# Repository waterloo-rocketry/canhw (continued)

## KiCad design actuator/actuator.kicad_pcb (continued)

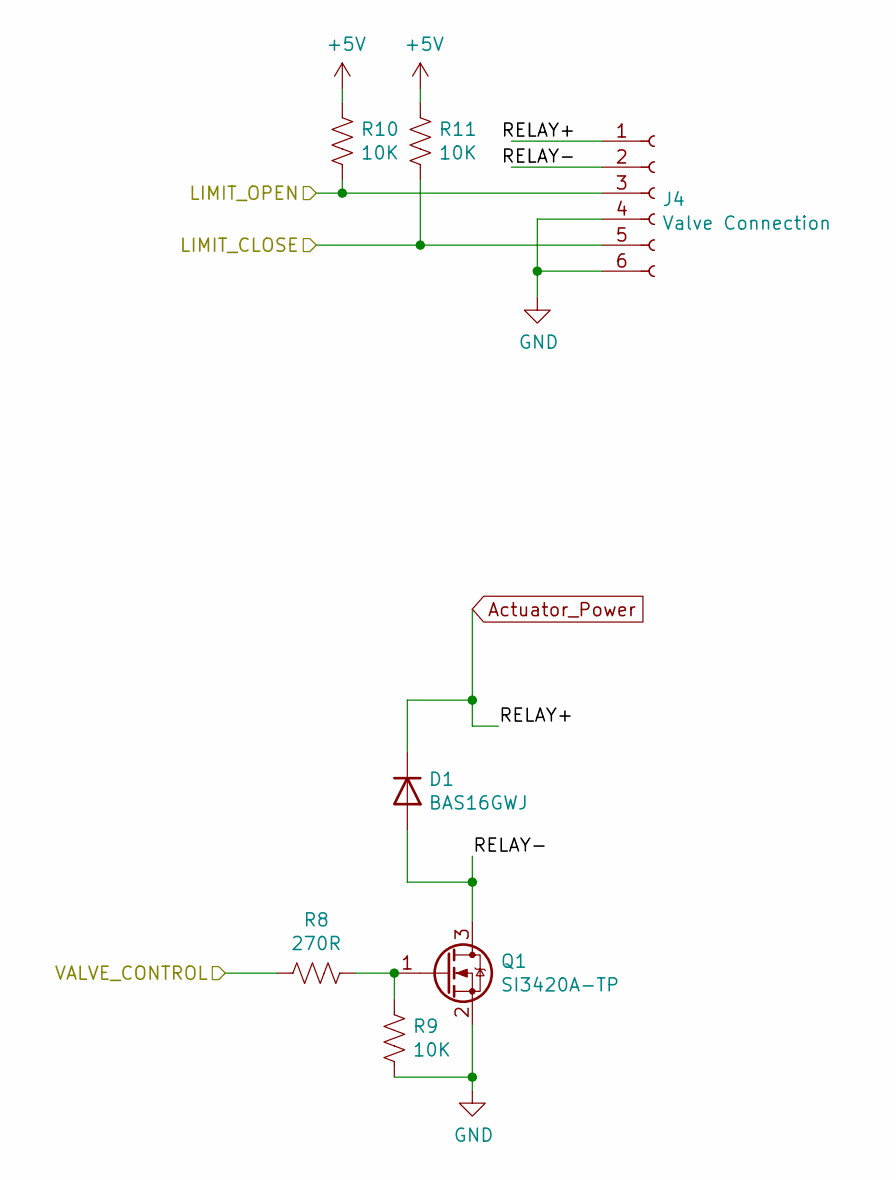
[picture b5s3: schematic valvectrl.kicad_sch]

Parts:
D1: BAS16GWJ; D_SOD-123
J4: Valve Connection; connector_Harwin_M80-5000642
Q1: SI3420A-TP; SOT-23_Handsoldering
R8: 270R; R_0805_2012Metric
R9, R10, R11: 10K; R_0805_2012Metric

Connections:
+5V: R10.1, R11.1; also elsewhere on the board
/MCU/LIMIT_CLOSE: J4.5, R11.2; also elsewhere on the board
/MCU/LIMIT_OPEN: J4.3, R10.2; also elsewhere on the board
/MCU/VALVE_CONTROL: R8.2; also elsewhere on the board
/Valve Control/RELAY-: D1.2 (A), J4.2, Q1.3 (D)
Actuator_Power: D1.1 (K), J4.1; also elsewhere on the board
GND: J4.4, J4.6, Q1.2 (S), R9.2; also elsewhere on the board
unnamed: Q1.1 (G), R8.1, R9.1

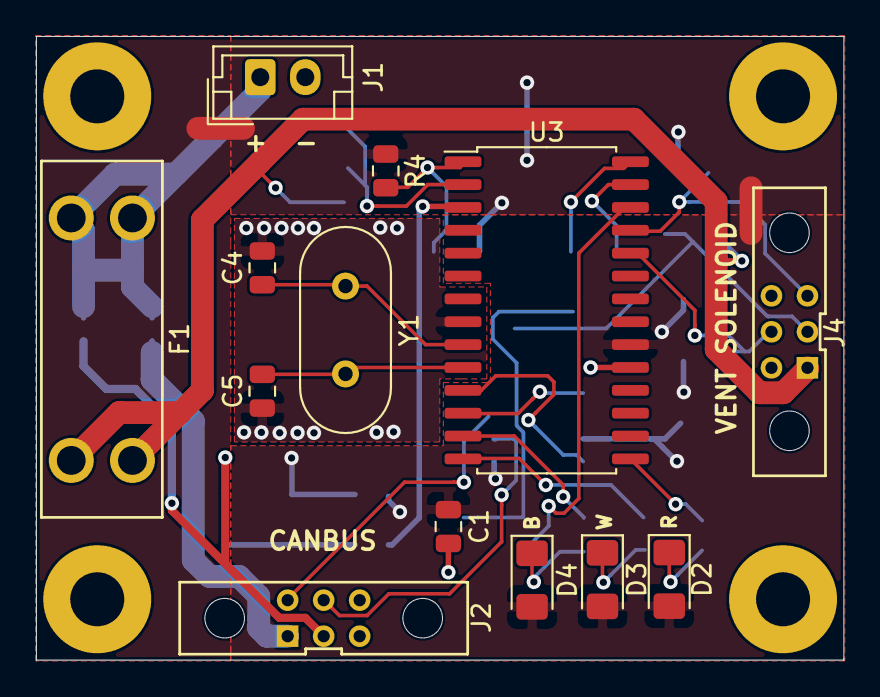
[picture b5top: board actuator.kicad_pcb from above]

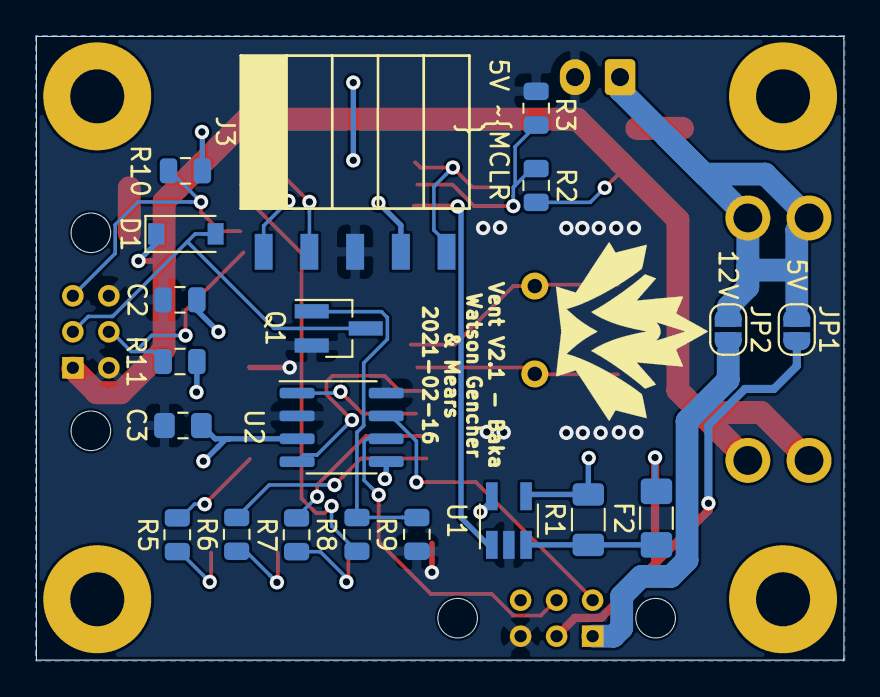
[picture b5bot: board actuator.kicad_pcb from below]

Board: 2 copper layers, 44.9 x 34.6 mm, 33 parts (20 on the bottom side), 29 nets.

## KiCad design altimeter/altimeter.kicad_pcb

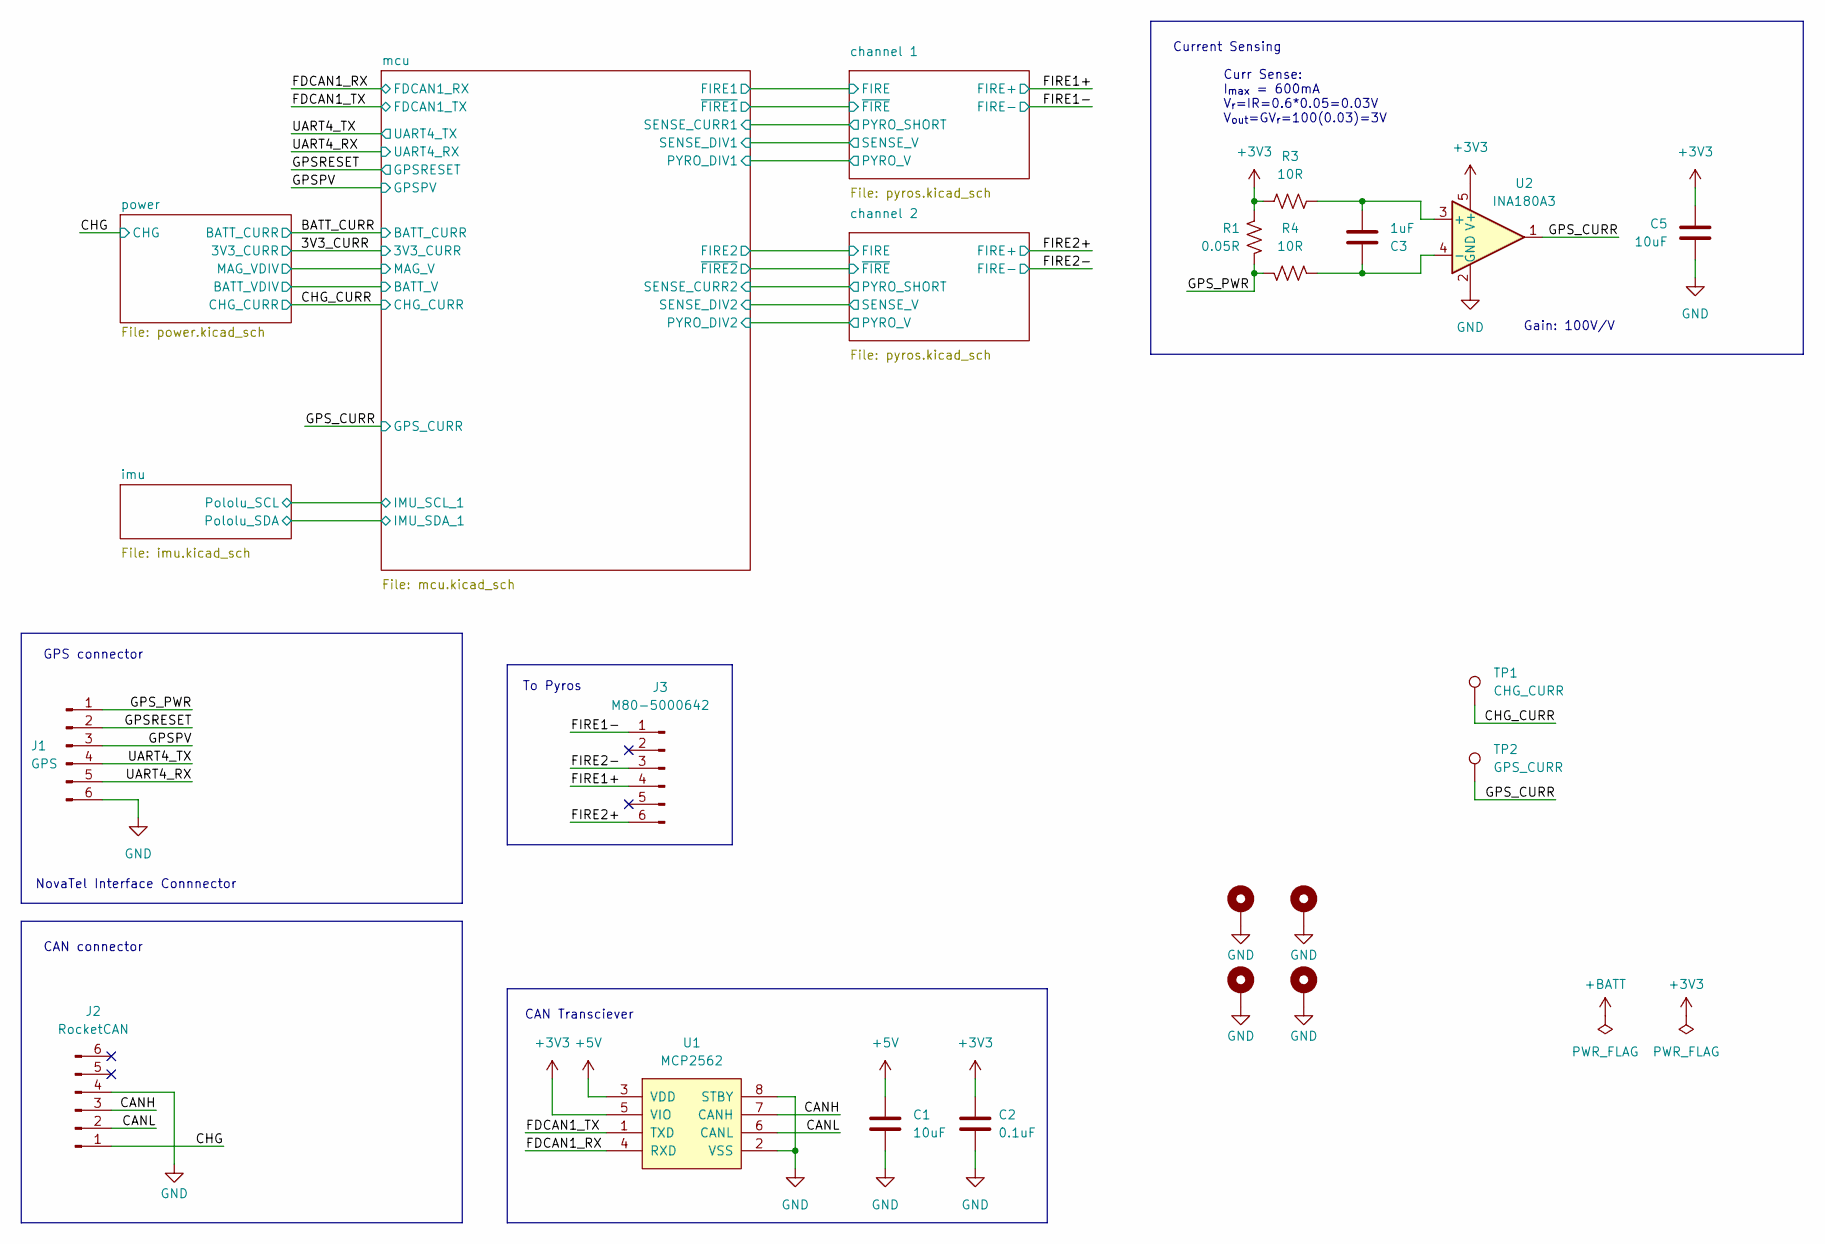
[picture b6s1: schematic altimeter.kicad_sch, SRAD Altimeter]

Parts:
C1, C5: 10uF; C_0805_2012Metric_Pad1.18x1.45mm_HandSolder
C2: 0.1uF; C_0805_2012Metric_Pad1.18x1.45mm_HandSolder
C3: 1uF; C_0805_2012Metric_Pad1.18x1.45mm_HandSolder
H1, H2, H3, H4: MountingHole_Pad; MountingHole_3.2mm_M3_Pad_Via
J1: GPS; connector_Harwin_G125–MG10605M4P
J2: RocketCAN; connector_Harwin_G125–MG10605M4P
J3: M80-5000642; connector_Harwin_M80-5000642
R1: 0.05R; R_0805_2012Metric_Pad1.20x1.40mm_HandSolder
R3, R4: 10R; R_0805_2012Metric_Pad1.20x1.40mm_HandSolder
TP1: CHG_CURR; TestPoint_Pad_1.0x1.0mm
TP2: GPS_CURR; TestPoint_Pad_1.0x1.0mm
U1: MCP2562; SOIC-8_3.9x4.9mm_P1.27mm
U2: INA180A3; SOT-23-5

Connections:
+5V: C1.1, U1.3 (VDD); also elsewhere on the board
/CANH: J2.3, U1.7 (CANH)
/CANL: J2.2, U1.6 (CANL)
/CHG: J2.1; also elsewhere on the board
/CHG_CURR: TP1.1; also elsewhere on the board
/FDCAN1_RX: U1.4 (RXD); also elsewhere on the board
/FDCAN1_TX: U1.1 (TXD); also elsewhere on the board
/FIRE1+: J3.4; also elsewhere on the board
/FIRE1-: J3.1; also elsewhere on the board
/FIRE2+: J3.6; also elsewhere on the board
/FIRE2-: J3.3; also elsewhere on the board
/GPSPV: J1.3; also elsewhere on the board
/GPSRESET: J1.2; also elsewhere on the board
/GPS_CURR: TP2.1, U2.1; also elsewhere on the board
/GPS_PWR: J1.1, R1.1, R4.2
/UART4_RX: J1.5; also elsewhere on the board
/UART4_TX: J1.4; also elsewhere on the board
GND: C1.2, C2.2, C5.2, H1.1, H2.1, H3.1, H4.1, J1.6, J2.4, U1.2 (VSS), U1.8 (STBY), U2.2 (GND); also elsewhere on the board
unnamed: C3.2, R3.2, U2.3 (+)
unnamed: C3.1, R4.1, U2.4 (-)

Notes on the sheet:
Current Sensing
CAN Transciever
GPS connector
To Pyros
CAN connector
Gain: 100V/V
NovaTel Interface Connnector
Curr Sense: I_{max} = 600mA V_{r}=IR=0.6*0.05=0.03V V_{out}=GV_{r}=100(0.03)=3V

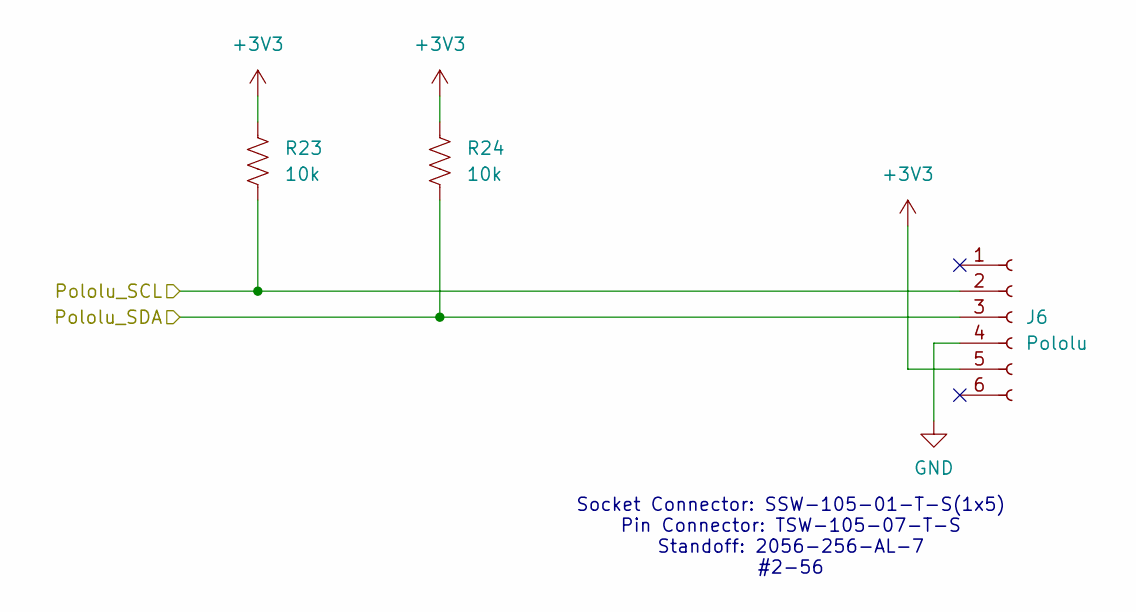
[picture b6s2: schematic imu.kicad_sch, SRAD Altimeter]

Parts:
J6: Pololu; PololuAltIMUv6
R23, R24: 10k; R_0805_2012Metric_Pad1.20x1.40mm_HandSolder

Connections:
/mcu/SWDIO: J6.4; also elsewhere on the board
GND: J6.1; also elsewhere on the board

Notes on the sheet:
Socket Connector: SSW-105-01-T-S(1x5) Pin Connector: TSW-105-07-T-S Standoff: 2056-256-AL-7 #2-56

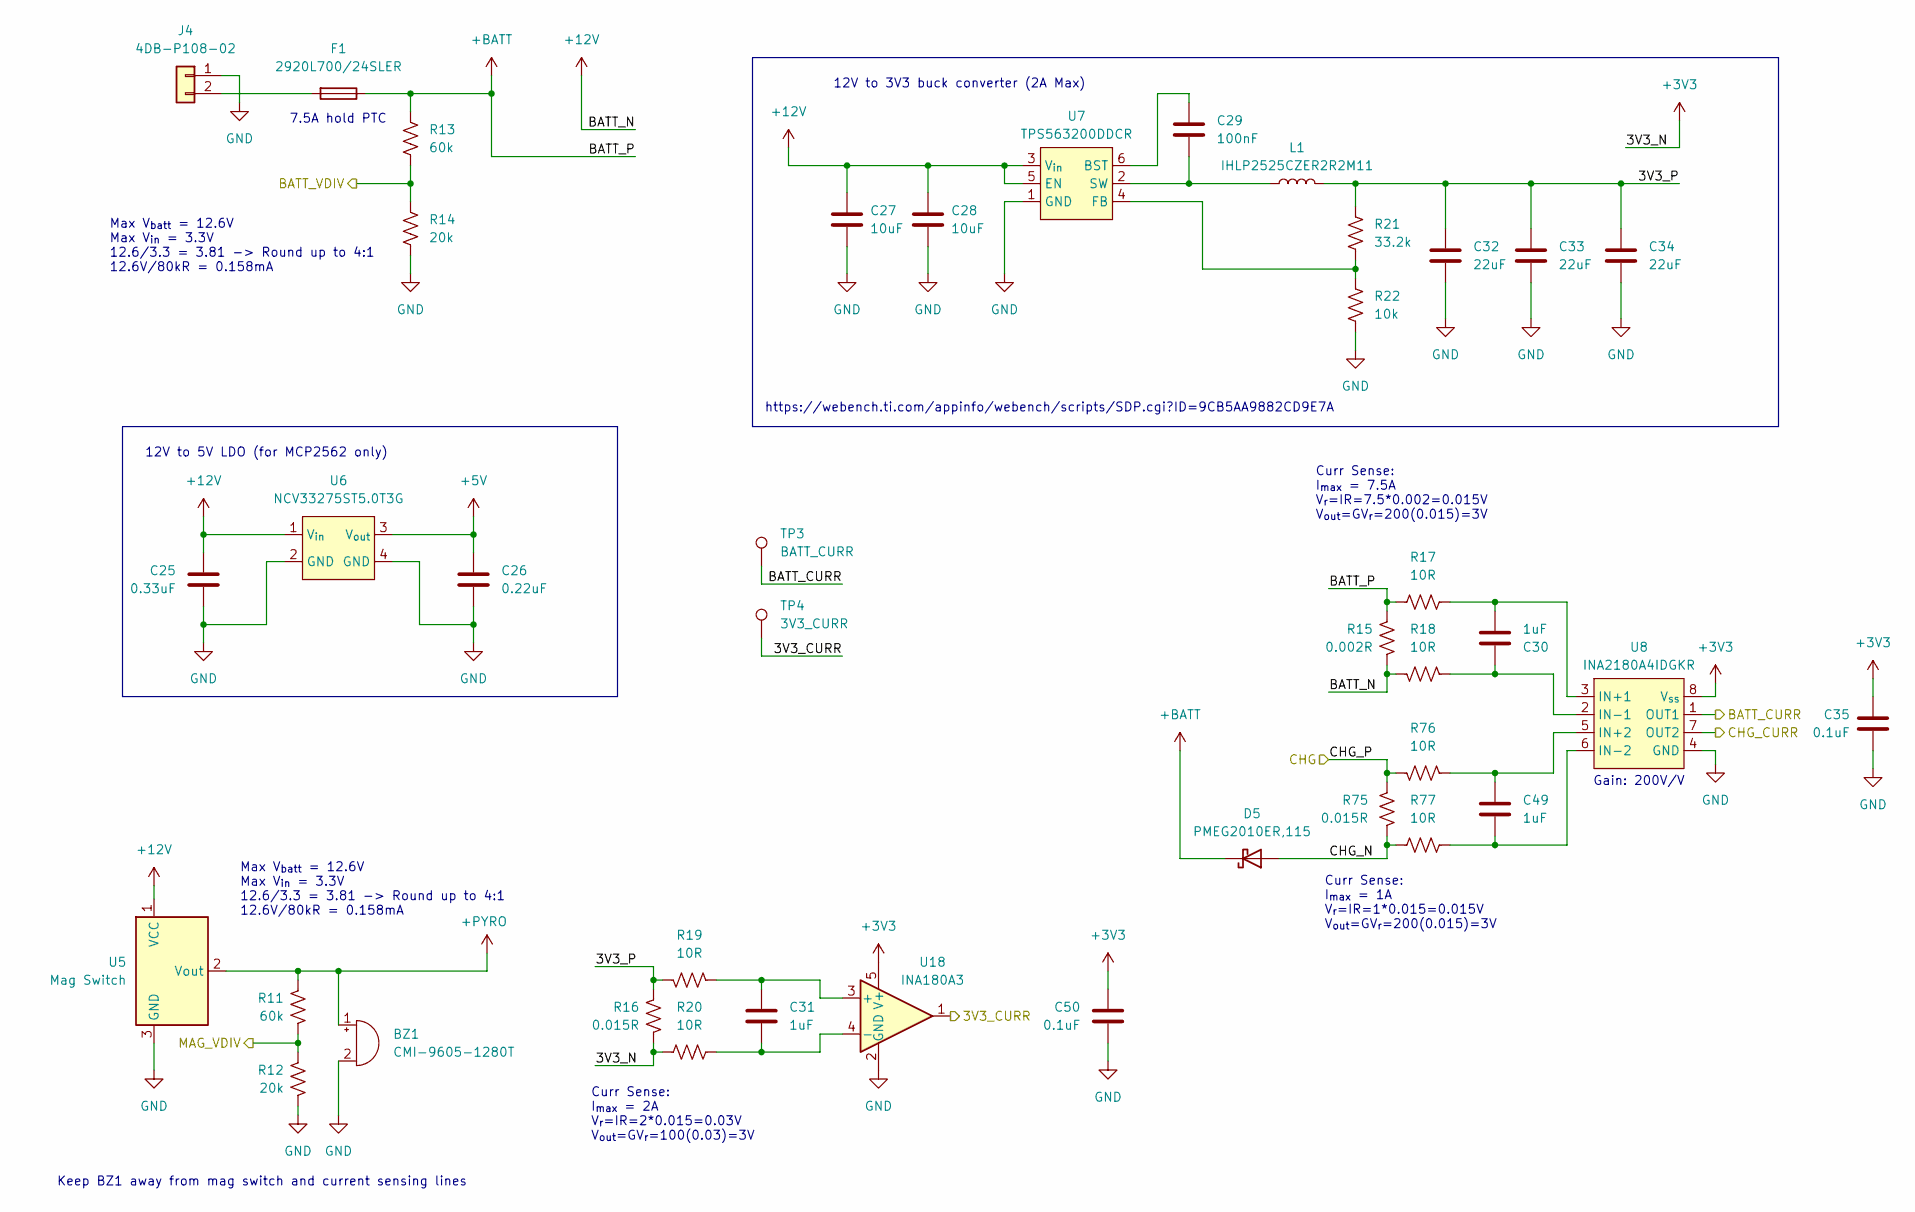
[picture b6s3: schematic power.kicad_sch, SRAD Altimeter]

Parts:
BZ1: CMI-9605-1280T; CUI_CMI-9605-1280T
C25: 0.33uF; C_0805_2012Metric_Pad1.18x1.45mm_HandSolder
C26: 0.22uF; C_0805_2012Metric_Pad1.18x1.45mm_HandSolder
C27, C28: 10uF; C_0805_2012Metric_Pad1.18x1.45mm_HandSolder
C29: 100nF; C_0805_2012Metric_Pad1.18x1.45mm_HandSolder
C30, C31, C49: 1uF; C_0805_2012Metric_Pad1.18x1.45mm_HandSolder
C32, C33, C34: 22uF; C_0805_2012Metric_Pad1.18x1.45mm_HandSolder
C35, C50: 0.1uF; C_0805_2012Metric_Pad1.18x1.45mm_HandSolder
D5: PMEG2010ER,115; Nexperia_CFP3_SOD-123W
F1: 2920L700/24SLER; Fuse_2920_7451Metric_Pad2.10x5.45mm_HandSolder
J4: 4DB-P108-02; TE_2-1437667-4
L1: IHLP2525CZER2R2M11; IND_IHLP-2525CZ_VIS
R11, R13: 60k; R_0805_2012Metric_Pad1.20x1.40mm_HandSolder
R12, R14: 20k; R_0805_2012Metric_Pad1.20x1.40mm_HandSolder
R15: 0.002R; R_0805_2012Metric_Pad1.20x1.40mm_HandSolder
R16, R75: 0.015R; R_0805_2012Metric_Pad1.20x1.40mm_HandSolder
R17, R18, R19, R20, R76, R77: 10R; R_0805_2012Metric_Pad1.20x1.40mm_HandSolder
R21: 33.2k; R_0805_2012Metric_Pad1.20x1.40mm_HandSolder
R22: 10k; R_0805_2012Metric_Pad1.20x1.40mm_HandSolder
TP3: BATT_CURR; TestPoint_Pad_1.0x1.0mm
TP4: 3V3_CURR; TestPoint_Pad_1.0x1.0mm
U5: Mag Switch
U6: NCV33275ST5.0T3G; SOT-223
U7: TPS563200DDCR; SOT-23-6
U8: INA2180A4IDGKR; VSSOP-8_3x3mm_P0.65mm
U18: INA180A3; SOT-23-5_HandSoldering

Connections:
+5V: C26.1, U6.3 (V_{out}); also elsewhere on the board
+12V: C25.1, C27.1, C28.1, R15.2, R18.2, U5.1 (VCC), U6.1 (V_{in}), U7.3 (V_{in}), U7.5 (EN)
+BATT: D5.1 (K), F1.1, R13.1, R15.1, R17.1
+PYRO: BZ1.1 (+), R11.1, U5.2 (Vout); also elsewhere on the board
/3V3_CURR: TP4.1, U18.1; also elsewhere on the board
/BATT_CURR: TP3.1, U8.1 (OUT1); also elsewhere on the board
/CHG: R75.2, R76.2; also elsewhere on the board
/CHG_CURR: U8.7 (OUT2); also elsewhere on the board
/mcu/BATT_V: R13.2, R14.1; also elsewhere on the board
/mcu/MAG_V: R11.2, R12.1; also elsewhere on the board
/power/3V3_P: C32.1, C33.1, C34.1, L1.1, R16.1, R19.2, R21.1
GND: BZ1.2 (-), C25.2, C26.2, C27.2, C28.2, C32.2, C33.2, C34.2, C35.2, C50.2, J4.1, R12.2, R14.2, R22.2, U5.3 (GND), U6.2 (GND), U6.4 (GND), U7.1 (GND), U8.4 (GND), U18.2 (GND); also elsewhere on the board
unnamed: F1.2, J4.2
unnamed: C29.1, U7.6 (BST)
unnamed: R21.2, R22.1, U7.4 (FB)
unnamed: C29.2, L1.2, U7.2 (SW)
unnamed: C30.2, R17.2, U8.3 (IN+1)
unnamed: C30.1, R18.1, U8.2 (IN-1)
unnamed 78: C49.2, R77.2, U8.6 (IN-2); also elsewhere on the board
unnamed: C31.1, R19.1, U18.3 (+)
unnamed: C31.2, R20.2, U18.4 (-)

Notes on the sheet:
Keep BZ1 away from mag switch and current sensing lines
Max V_{batt} = 12.6V Max V_{in} = 3.3V 12.6/3.3 = 3.81 -> Round up to 4:1 12.6V/80kR = 0.158mA
Gain: 200V/V
12V to 5V LDO (for MCP2562 only)
https://webench.ti.com/appinfo/webench/scripts/SDP.cgi?ID=9CB5AA9882CD9E7A
Curr Sense: I_{max} = 1A V_{r}=IR=1*0.015=0.015V V_{out}=GV_{r}=200(0.015)=3V
7.5A hold PTC
Curr Sense: I_{max} = 2A V_{r}=IR=2*0.015=0.03V V_{out}=GV_{r}=100(0.03)=3V
Curr Sense: I_{max} = 7.5A V_{r}=IR=7.5*0.002=0.015V V_{out}=GV_{r}=200(0.015)=3V
12V to 3V3 buck converter (2A Max)

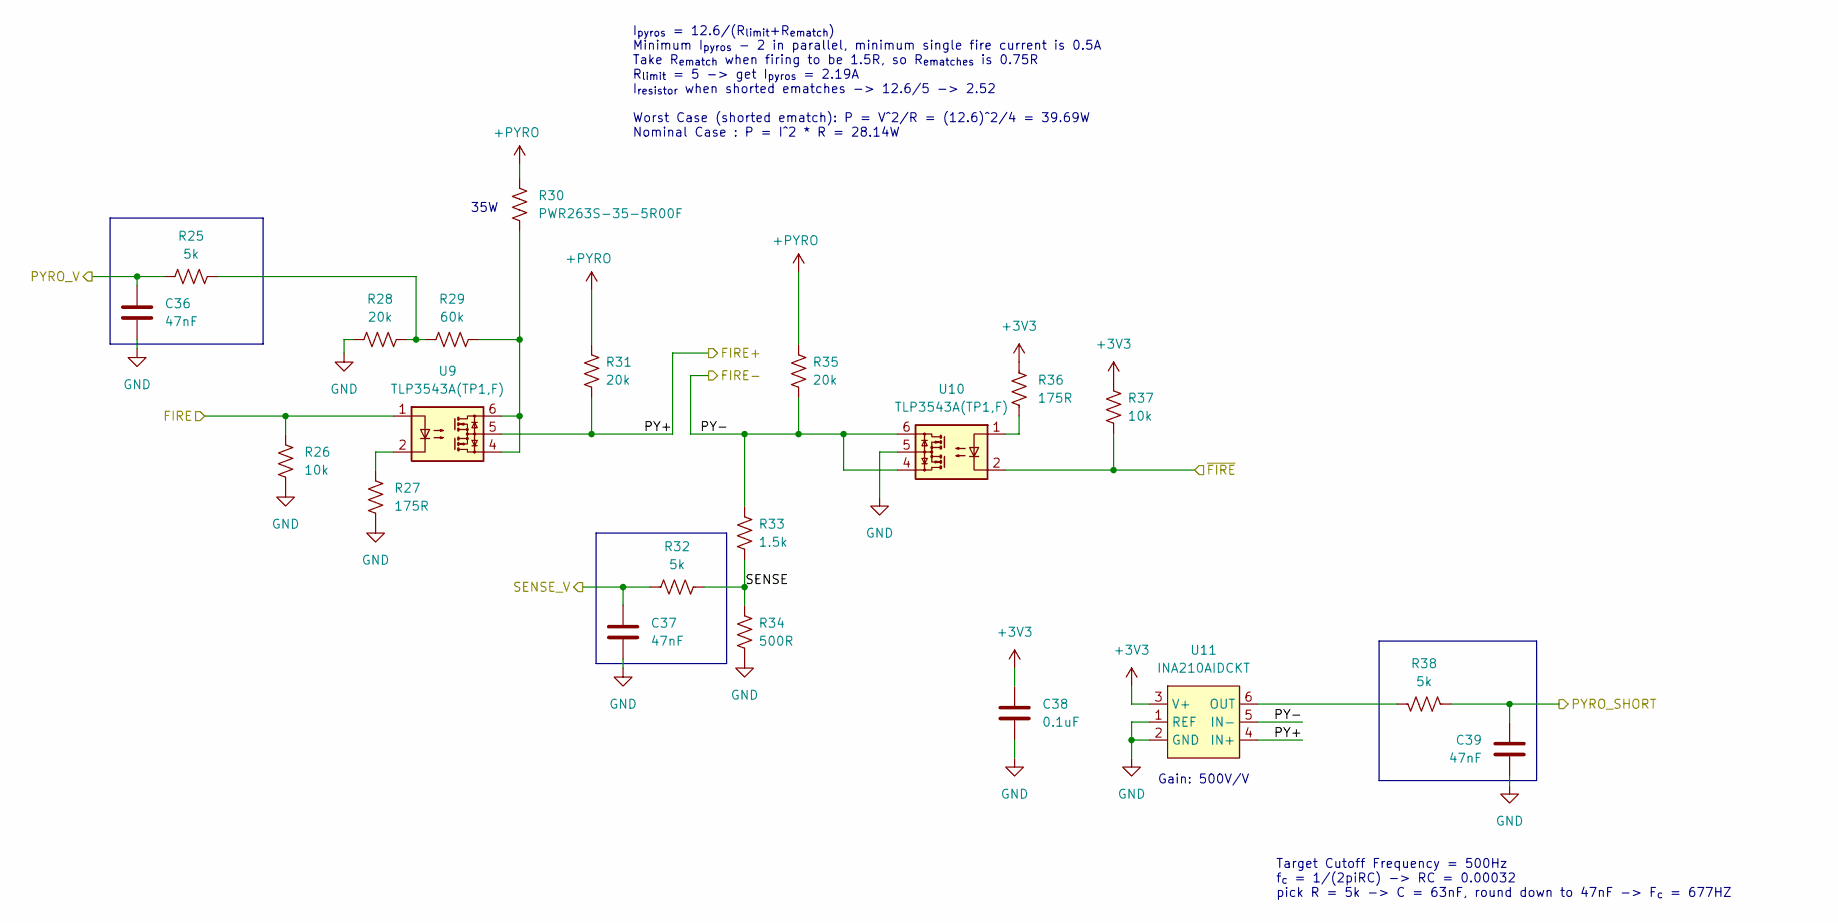
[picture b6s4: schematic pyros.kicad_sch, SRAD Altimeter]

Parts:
C36, C37, C39: 47nF; C_0805_2012Metric_Pad1.18x1.45mm_HandSolder
C38: 0.1uF; C_0805_2012Metric_Pad1.18x1.45mm_HandSolder
R25, R32, R38: 5k; R_0805_2012Metric_Pad1.20x1.40mm_HandSolder
R26, R37: 10k; R_0805_2012Metric_Pad1.20x1.40mm_HandSolder
R27, R36: 175R; R_0805_2012Metric_Pad1.20x1.40mm_HandSolder
R28, R31, R35: 20k; R_0805_2012Metric_Pad1.20x1.40mm_HandSolder
R29: 60k; R_0805_2012Metric_Pad1.20x1.40mm_HandSolder
R30: PWR263S-35-5R00F; RES_PWR263S_BRN
R33: 1.5k; R_0805_2012Metric_Pad1.20x1.40mm_HandSolder
R34: 500R; R_0805_2012Metric_Pad1.20x1.40mm_HandSolder
U9, U10: TLP3543A(TP1,F); TLP3543A__6P4X7P12_TOS
U11: INA210AIDCKT; SOT-363_SC-70-6_Handsoldering

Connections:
+PYRO: R30.2, R31.1, R35.1; also elsewhere on the board
/FIRE1+: R31.2, U9.5, U11.4 (IN+); also elsewhere on the board
/FIRE1-: R33.1, R35.2, U10.4, U10.6, U11.5 (IN-); also elsewhere on the board
/channel 1/FIRE: R26.1, U9.1; also elsewhere on the board
/channel 1/PYRO_SHORT: C39.1, R38.1; also elsewhere on the board
/channel 1/PYRO_V: C36.1, R25.1; also elsewhere on the board
/channel 1/SENSE: R32.2, R33.2, R34.1
/channel 1/SENSE_V: C37.1, R32.1; also elsewhere on the board
/channel 1/~FIRE: R37.2, U10.2; also elsewhere on the board
GND: C36.2, C37.2, C38.2, C39.2, R26.2, R27.2, R28.1, R34.2, U10.5, U11.1 (REF), U11.2 (GND); also elsewhere on the board
unnamed: R25.2, R28.2, R29.1
unnamed: R27.1, U9.2
unnamed: R29.2, R30.1, U9.4, U9.6
unnamed: R36.2, U10.1
unnamed: R38.2, U11.6 (OUT)

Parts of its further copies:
C40, C41, C43: 47nF; C_0805_2012Metric_Pad1.18x1.45mm_HandSolder
C42: 0.1uF; C_0805_2012Metric_Pad1.18x1.45mm_HandSolder
R39, R46, R52: 5k; R_0805_2012Metric_Pad1.20x1.40mm_HandSolder
R40, R51: 10k; R_0805_2012Metric_Pad1.20x1.40mm_HandSolder
R41, R50: 175R; R_0805_2012Metric_Pad1.20x1.40mm_HandSolder
R42, R45, R49: 20k; R_0805_2012Metric_Pad1.20x1.40mm_HandSolder
R43: 60k; R_0805_2012Metric_Pad1.20x1.40mm_HandSolder
R44: PWR263S-35-5R00F; RES_PWR263S_BRN
R47: 1.5k; R_0805_2012Metric_Pad1.20x1.40mm_HandSolder
R48: 500R; R_0805_2012Metric_Pad1.20x1.40mm_HandSolder
U12, U13: TLP3543A(TP1,F); TLP3543A__6P4X7P12_TOS
U14: INA210AIDCKT; SOT-363_SC-70-6_Handsoldering

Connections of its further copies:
+PYRO: R44.2, R45.1, R49.1; also elsewhere on the board
/FIRE2+: R45.2, U12.5, U14.4 (IN+); also elsewhere on the board
/FIRE2-: R47.1, R49.2, U13.4, U13.6, U14.5 (IN-); also elsewhere on the board
/channel 2/FIRE: R40.1, U12.1; also elsewhere on the board
/channel 2/PYRO_SHORT: C43.1, R52.1; also elsewhere on the board
/channel 2/PYRO_V: C40.1, R39.1; also elsewhere on the board
/channel 2/SENSE: R46.2, R47.2, R48.1
/channel 2/SENSE_V: C41.1, R46.1; also elsewhere on the board
/channel 2/~FIRE: R51.2, U13.2; also elsewhere on the board
GND: C40.2, C41.2, C42.2, C43.2, R40.2, R41.2, R42.1, R48.2, U13.5, U14.1 (REF), U14.2 (GND); also elsewhere on the board
unnamed: R39.2, R42.2, R43.1
unnamed: R41.1, U12.2
unnamed: R43.2, R44.1, U12.4, U12.6
unnamed: R50.2, U13.1
unnamed: R52.2, U14.6 (OUT)

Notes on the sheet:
Target Cutoff Frequency = 500Hz f_{c} = 1/(2piRC) -> RC = 0.00032 pick R = 5k -> C = 63nF, round down to 47nF -> F_{c} = 677HZ
I_{pyros} = 12.6/(R_{limit}+R_{ematch}) Minimum I_{pyros} - 2 in parallel, minimum single fire current is 0.5A Take R_{ematch} when firing to be 1.5R, so R_{ematches} is 0.75R R_{limit} = 5 -> get I_{pyros} = 2.19A I_{resistor} when shorted ematches -> 12.6/5 -> 2.52 Worst Case (shorted ematch): P 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
Gain: 500V/V
35W

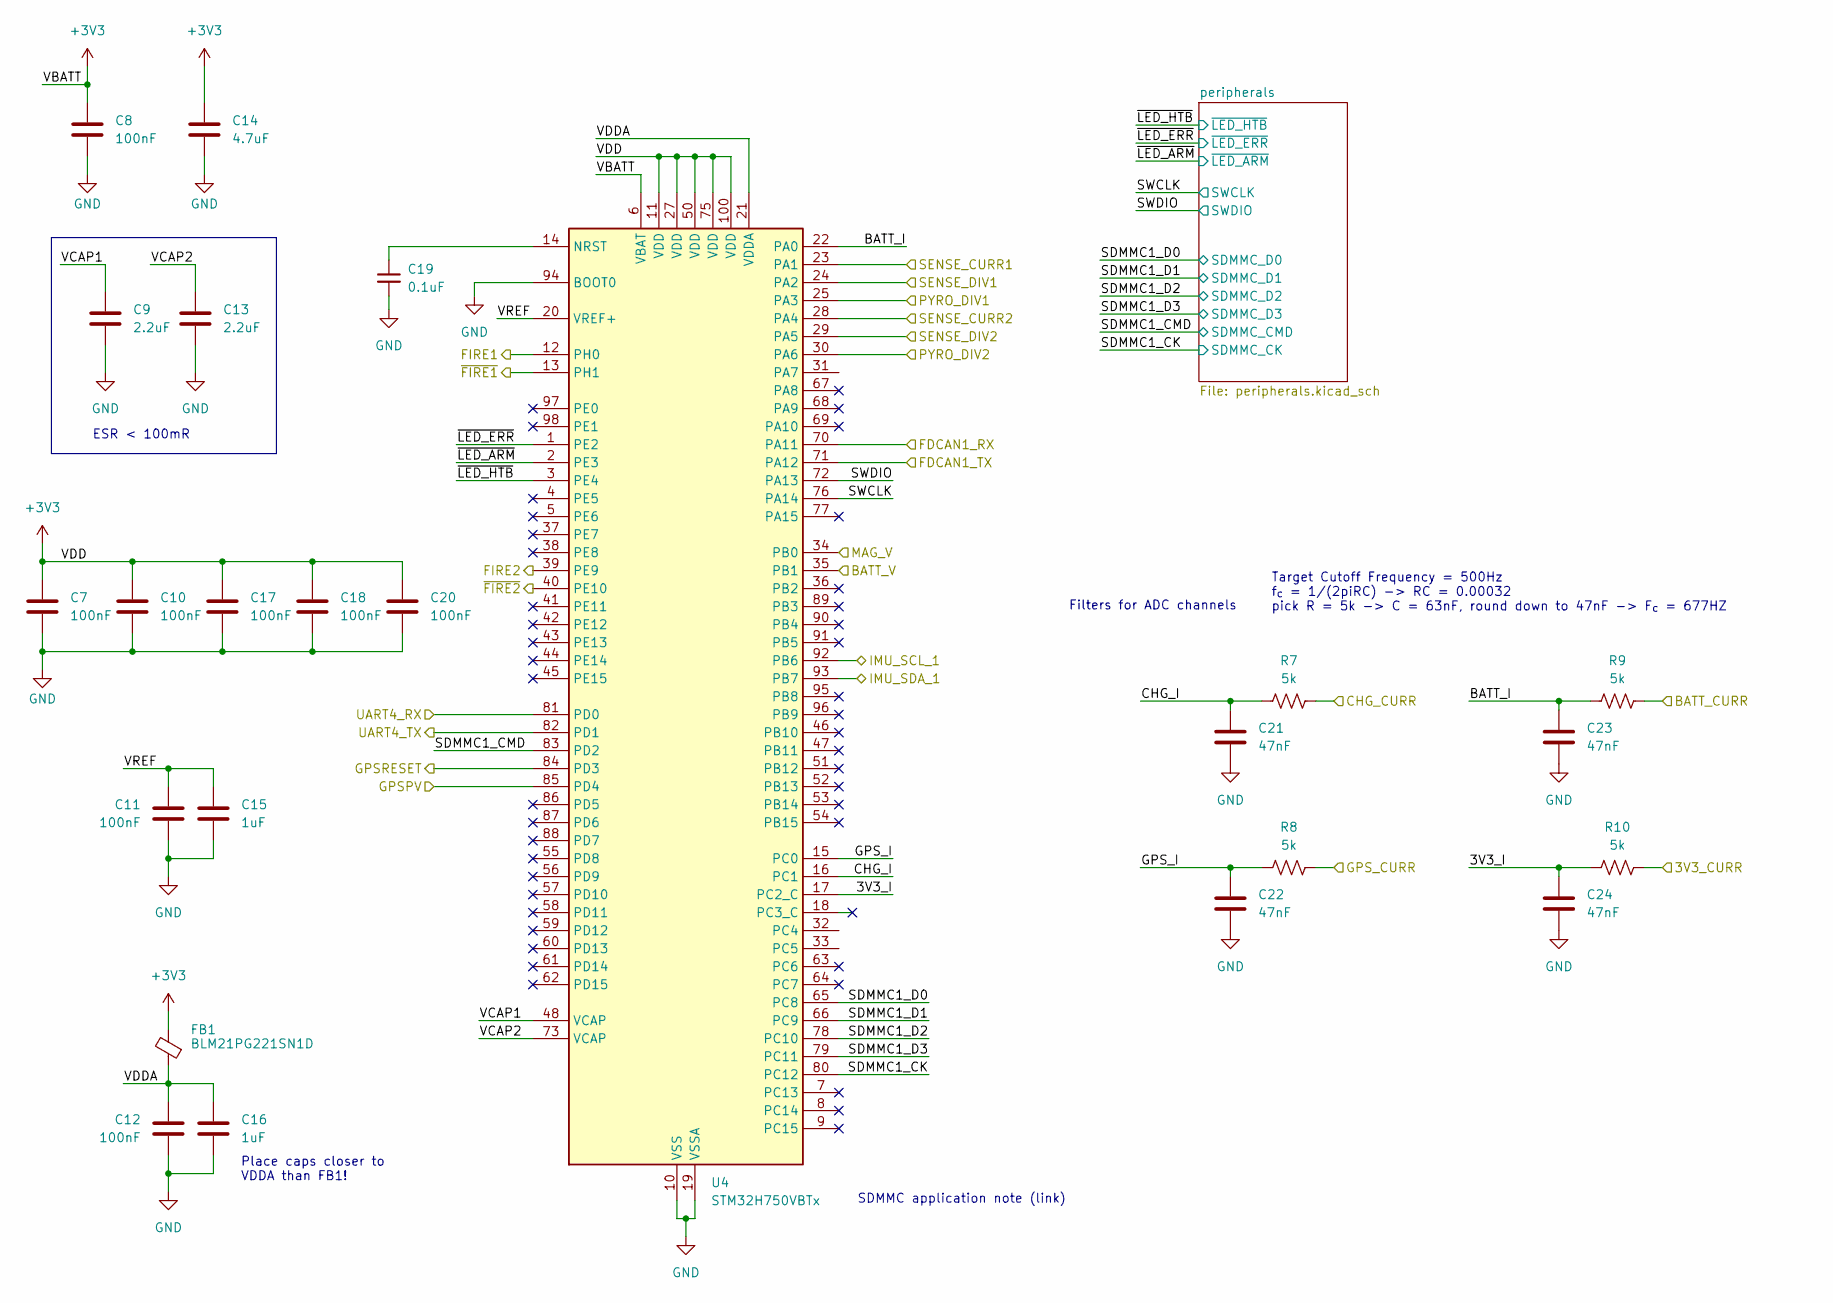
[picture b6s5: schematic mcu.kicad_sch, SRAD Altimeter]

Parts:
C7, C8, C10, C11, C12, C17, C18, C20: 100nF; C_0805_2012Metric_Pad1.18x1.45mm_HandSolder
C9, C13: 2.2uF; C_0805_2012Metric_Pad1.18x1.45mm_HandSolder
C14: 4.7uF; C_0805_2012Metric_Pad1.18x1.45mm_HandSolder
C15, C16: 1uF; C_0805_2012Metric_Pad1.18x1.45mm_HandSolder
C19: 0.1uF; C_0805_2012Metric_Pad1.18x1.45mm_HandSolder
C21, C22, C23, C24: 47nF; C_0805_2012Metric_Pad1.18x1.45mm_HandSolder
FB1: BLM21PG221SN1D; L_0805_2012Metric_Pad1.15x1.40mm_HandSolder
R7, R8, R9, R10: 5k; R_0805_2012Metric_Pad1.20x1.40mm_HandSolder
U4: STM32H750VBTx; LQFP-100_14x14mm_P0.5mm

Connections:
/3V3_CURR: R10.2; also elsewhere on the board
/BATT_CURR: R9.2; also elsewhere on the board
/CHG_CURR: R7.2; also elsewhere on the board
/FDCAN1_RX: U4.70 (PA11); also elsewhere on the board
/FDCAN1_TX: U4.71 (PA12); also elsewhere on the board
/GPSPV: U4.85 (PD4); also elsewhere on the board
/GPSRESET: U4.84 (PD3); also elsewhere on the board
/GPS_CURR: R8.2; also elsewhere on the board
/UART4_RX: U4.81 (PD0); also elsewhere on the board
/UART4_TX: U4.82 (PD1); also elsewhere on the board
/channel 1/FIRE: U4.12 (PH0); also elsewhere on the board
/channel 1/PYRO_SHORT: U4.23 (PA1); also elsewhere on the board
/channel 1/PYRO_V: U4.25 (PA3); also elsewhere on the board
/channel 1/SENSE_V: U4.24 (PA2); also elsewhere on the board
/channel 1/~FIRE: U4.13 (PH1); also elsewhere on the board
/channel 2/FIRE: U4.39 (PE9); also elsewhere on the board
/channel 2/PYRO_SHORT: U4.28 (PA4); also elsewhere on the board
/channel 2/PYRO_V: U4.30 (PA6); also elsewhere on the board
/channel 2/SENSE_V: U4.29 (PA5); also elsewhere on the board
/channel 2/~FIRE: U4.40 (PE10); also elsewhere on the board
/mcu/3V3_I: C24.1, R10.1, U4.17 (PC2_C)
/mcu/BATT_I: C23.1, R9.1, U4.22 (PA0)
/mcu/BATT_V: U4.35 (PB1); also elsewhere on the board
/mcu/CHG_I: C21.1, R7.1, U4.16 (PC1)
/mcu/GPS_I: C22.1, R8.1, U4.15 (PC0)
/mcu/MAG_V: U4.34 (PB0); also elsewhere on the board
/mcu/SDMMC1_CK: U4.80 (PC12); also elsewhere on the board
/mcu/SDMMC1_CMD: U4.83 (PD2); also elsewhere on the board
/mcu/SDMMC1_D0: U4.65 (PC8); also elsewhere on the board
/mcu/SDMMC1_D1: U4.66 (PC9); also elsewhere on the board
/mcu/SDMMC1_D2: U4.78 (PC10); also elsewhere on the board
/mcu/SDMMC1_D3: U4.79 (PC11); also elsewhere on the board
/mcu/SWDIO: U4.72 (PA13); also elsewhere on the board
/mcu/VCAP1: C9.1, U4.48 (VCAP)
/mcu/VCAP2: C13.1, U4.73 (VCAP)
/mcu/VDDA: C12.1, C16.1, FB1.1, U4.21 (VDDA)
/mcu/VREF: C11.1, C15.1, U4.20 (VREF+)
/mcu/~LED_ARM: U4.2 (PE3); also elsewhere on the board
/mcu/~LED_ERR: U4.1 (PE2); also elsewhere on the board
/mcu/~LED_HTB: U4.3 (PE4); also elsewhere on the board
GND: C7.2, C8.2, C9.2, C10.2, C11.2, C12.2, C13.2, C14.2, C15.2, C16.2, C17.2, C18.2, C19.2, C20.2, C21.2, C22.2, C23.2, C24.2, U4.10 (VSS), U4.19 (VSSA), U4.26 (VSS), U4.49 (VSS), U4.74 (VSS), U4.94 (BOOT0), U4.99 (VSS); also elsewhere on the board
unnamed: C19.1, U4.14 (NRST)

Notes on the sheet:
Filters for ADC channels
Place caps closer to VDDA than FB1!
ESR < 100mR
SDMMC application note (link)
Target Cutoff Frequency = 500Hz f_{c} = 1/(2piRC) -> RC = 0.00032 pick R = 5k -> C = 63nF, round down to 47nF -> F_{c} = 677HZ

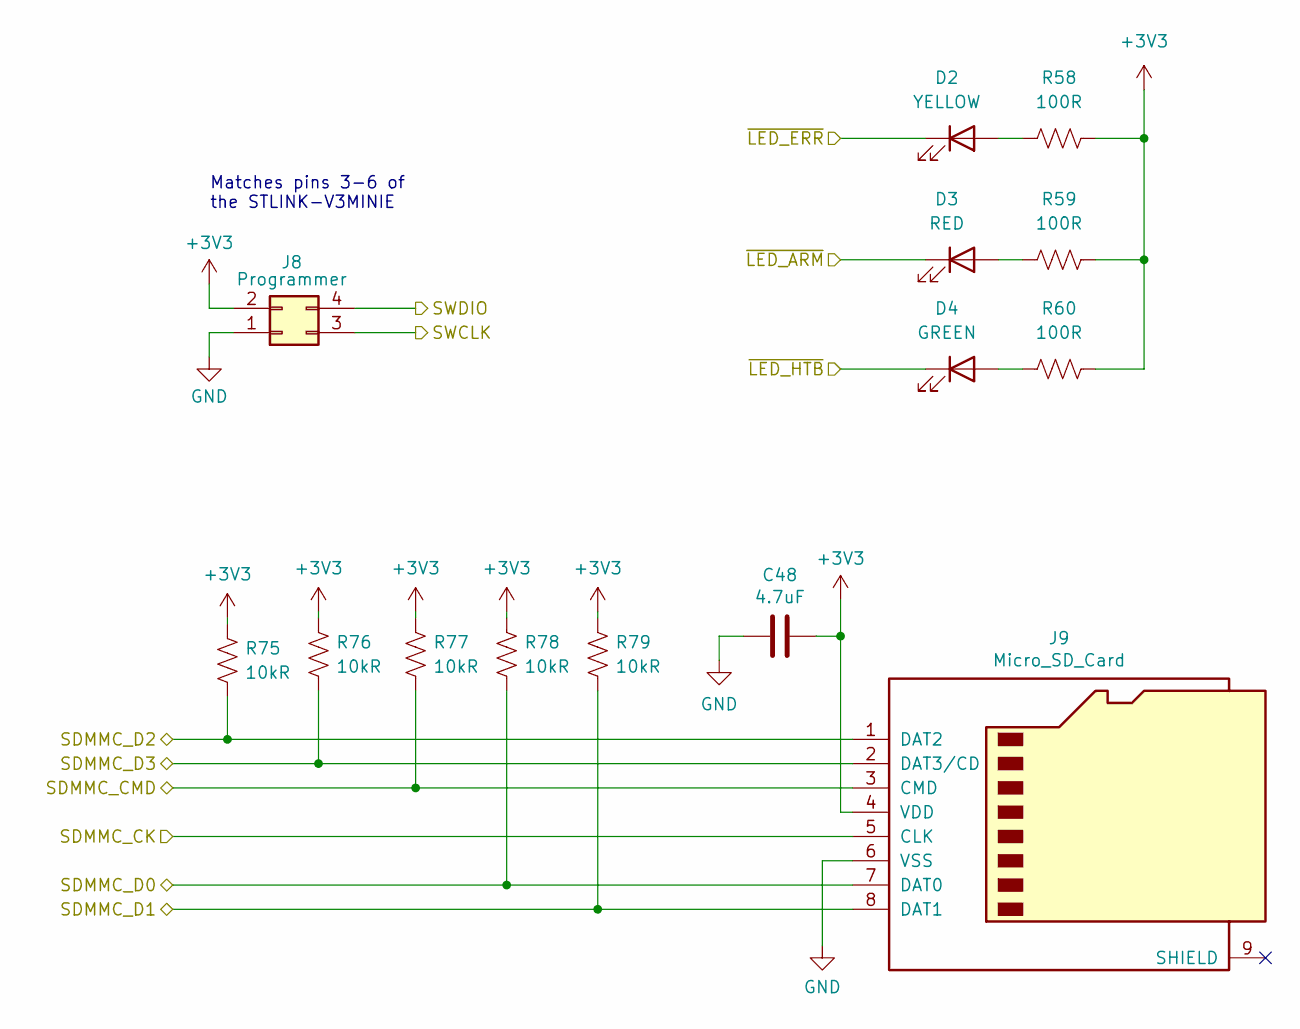
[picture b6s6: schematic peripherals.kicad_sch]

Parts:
C48: 4.7uF; C_0805_2012Metric_Pad1.18x1.45mm_HandSolder
D2: YELLOW; D_1206_3216Metric_Pad1.42x1.75mm_HandSolder
D3: RED; D_1206_3216Metric_Pad1.42x1.75mm_HandSolder
D4: GREEN; D_1206_3216Metric_Pad1.42x1.75mm_HandSolder
J8: Programmer; PinSocket_2x02_P1.27mm_Vertical_SMD
J9: Micro_SD_Card; microSD_Molex_WM6698CT-ND
R58, R59, R60: 100R; R_0805_2012Metric_Pad1.20x1.40mm_HandSolder
R75, R76, R77, R78, R79: 10kR; R_0805_2012Metric_Pad1.20x1.40mm_HandSolder

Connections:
/CHG: J9.1 (DAT2), J9.2 (DAT3/CD), R75.2, R76.2; also elsewhere on the board
/mcu/~LED_ARM: D3.1 (K); also elsewhere on the board
/mcu/~LED_ERR: D2.1 (K); also elsewhere on the board
/mcu/~LED_HTB: D4.1 (K); also elsewhere on the board
GND: C48.2, J8.1, J9.6 (VSS); also elsewhere on the board
unnamed 56: D2.2 (A), R58.1; also elsewhere on the board
unnamed 57: D3.2 (A), R59.1; also elsewhere on the board
unnamed 58: D4.2 (A), R60.1; also elsewhere on the board
unnamed: J9.7 (DAT0), R78.2
unnamed: J9.8 (DAT1), R79.2
unnamed 78: J9.3 (CMD), R77.2; also elsewhere on the board

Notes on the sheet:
Matches pins 3-6 of the STLINK-V3MINIE

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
